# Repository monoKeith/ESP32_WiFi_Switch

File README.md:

# ESP32_WiFi_Switch

This project include hardware design and firmware implementation for a ESP32-S2 powered network accessable on/off switch.

This switch have an 128*64 OLED I2C display to show information. User can turn on/off the switch from HomeKit, physical button, or web interface.

Powered by a [ESP32-S2-Wroom](https://www.espressif.com/sites/default/files/documentation/esp32-s2-wroom_esp32-s2-wroom-i_datasheet_en.pdf). Because the use of ESP32-S2 specific hardware timer library, firmware might have compatibility issue on older (or different) ESP32 models.

## Hardware

PCB printed | PCB etched
:-------------------------:|:-------------------------:
 | 

Soldered | Bread board
:-------------------------:|:-------------------------:
 | 

Single layer PCB designed with [KiCad](https://www.kicad.org/) in `./breakout_board`. This is only useful for starting with only a [module](https://www.espressif.com/en/products/modules), unnecessary if you already have a dev board. Requires ESP32-S2-WROOM library from [this](https://github.com/eggsampler/ESP32-S2-Breakout) breakout board design.

Connected devices includes:

* 3 buttons pull-down to ground (resistors are optional)

* 1 mono-color 128*64 OLED I2C display [like this one](https://www.adafruit.com/product/326) (These are like $2 - $3 each on Aliexpress)

* external circuit to drive a relay (or MOSFET) from a GPIO pin. (I use a transistor to drive a 5V relay)

## Firmware

Firmware was implemented in C++ using PlatformIO arduino framework. Each part of the firmware is run a task of FreeRTOS. PlatformIO was initialized with [adafruit MagTag](https://www.adafruit.com/product/4800) configuration (which uses the same module), because ESP32-S2 Dev Board does not offer support for arduino framework.

Configure properties of firmware in `Firmware/src/config.h` according to how hardwares are connectred, and Wi-Fi credential. (ESP32-S2 allows any 2 GPIO pins to run I2C, connecting I2C display to any 2 GPIO pins should work)

### Functionalities

* [Automatically connect to Wi-Fi](https://randomnerdtutorials.com/esp32-useful-wi-fi-functions-arduino/) with credentials configured in `config.h`

* [Get current time from time server](https://randomnerdtutorials.com/esp32-date-time-ntp-client-server-arduino/)

* Sync time with time server periodically (uses [ESP32-S2 hardware timer](https://github.com/khoih-prog/ESP32TimerInterrupt/blob/master/examples/TimerInterruptTest/TimerInterruptTest.ino))

* [Turn on / off the switch from web interface](https://randomnerdtutorials.com/esp32-web-server-arduino-ide/)

* Turn on / off the switch with buttons, (white = on, gray = off)

* Press black button to cycle through display mode [REGULAR] -> [DEBUG] -> [OFF]

* Show message on screen when switch is being turn on / off, message stay on screen for 3000ms by default (configurable in `config.h`)

### Display

[REGULAR] mode:

* only shows current time

* display message in full screen if any.

[DEBUG] mode:

* on / off status of the switch

* current time

* Wi-Fi connection status, IP address and RSSI

* display message if any, otherwise show the time of last clock synchronization.

* time mark in ms for current message to hit it's 3000ms lifetime

* uptime in ms

REGULAR | REGULAR-MESSAGE| DEBUG
:-------------------------:|:-------------------------:|:-------------------------:
 |  | 

### PlatformIO Libraries

* [esp8266-oled-ssd1306](https://github.com/ThingPulse/esp8266-oled-ssd1306)

* [ESP32TimerInterrupt](https://github.com/khoih-prog/ESP32TimerInterrupt)

* [ESPAsyncWebServer](https://github.com/me-no-dev/ESPAsyncWebServer/)

### HomeBridge Plugin

To make the switch accessable from [iOS Home](https://www.apple.com/ca/ios/home/), a separate [HomeBridge](https://homebridge.io/) server is required. I am running the HomeBridge server on a [RaspberryPi Zero W](https://www.raspberrypi.com/products/raspberry-pi-zero-w/).

Install this plugin: [homebridge-http-switch](https://github.com/Supereg/homebridge-http-switch#readme) in HomeBridge, change settings (fill in the ip address and name):

```
{
    "accessory": "HTTP-SWITCH",
    "name": "<name-display-in-Home>",
    "switchType": "stateful",
    "serialNumber": "<fill-in-anything-here>",
    "onUrl": "http://<ip-of-esp32>:80/homebridge/switch/on",
    "offUrl": "http://<ip-of-esp32>:80/homebridge/switch/off",
    "statusUrl": "http://<ip-of-esp32>:80/homebridge/switch/status"
}
```

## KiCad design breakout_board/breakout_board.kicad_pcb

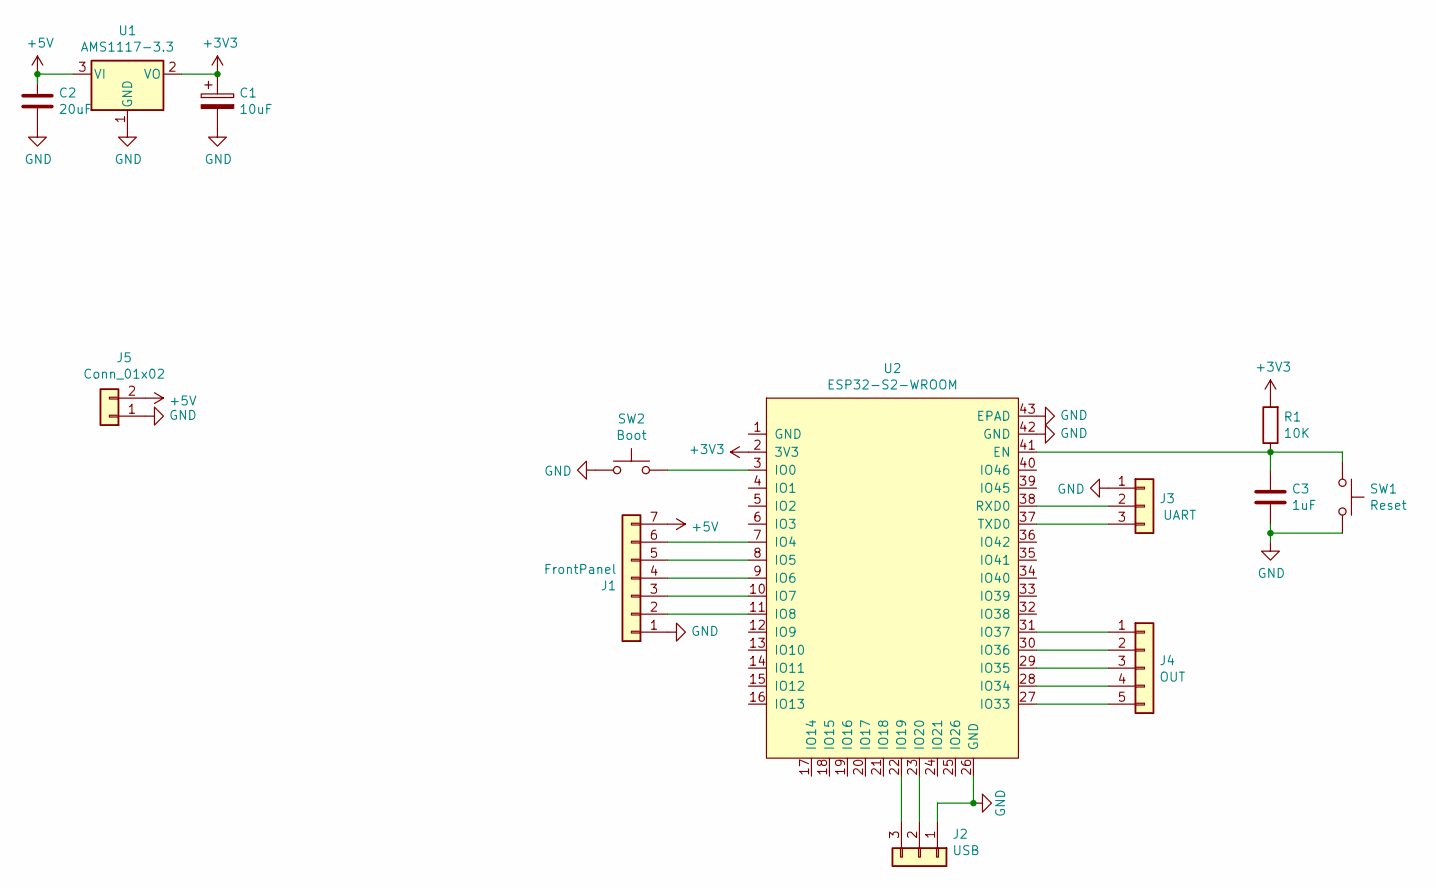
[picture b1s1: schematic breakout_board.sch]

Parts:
C1: 10uF; CP_Elec_5x5.9
C2: 20uF; CP_Elec_5x5.9
C3: 1uF; CP_Elec_5x5.9
J1: FrontPanel; PinHeader_1x07_P2.54mm_Vertical
J2: USB; PinHeader_1x03_P2.54mm_Vertical
J3: UART; PinHeader_1x03_P2.54mm_Vertical
J4: OUT; PinHeader_1x05_P2.54mm_Vertical
J5: Conn_01x02; PinHeader_1x02_P2.54mm_Vertical
R1: 10K; R_Axial_DIN0207_L6.3mm_D2.5mm_P10.16mm_Horizontal
SW1: Reset; SW_Push_1P1T_NO_Vertical_Wuerth_434133025816
SW2: Boot; SW_Push_1P1T_NO_Vertical_Wuerth_434133025816
U1: AMS1117-3.3; SOT-223-3_TabPin2
U2: ESP32-S2-WROOM

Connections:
+3V3: C1.1, R1.2, U1.2 (VO), U2.2 (3V3)
+5V: C2.1, J1.7, J5.2, U1.3 (VI)
GND: C1.2, C2.2, C3.2, J1.1, J2.1, J3.1, J5.1, SW1.2, SW2.1, U1.1 (GND), U2.26 (GND), U2.42 (GND), U2.43 (EPAD)
unnamed: C3.1, R1.1, SW1.1, U2.41 (EN)
unnamed: J1.2, U2.11 (IO8)
unnamed: J1.3, U2.10 (IO7)
unnamed: J1.4, U2.9 (IO6)
unnamed: J1.5, U2.8 (IO5)
unnamed: J1.6, U2.7 (IO4)
unnamed: J2.2, U2.23 (IO20)
unnamed: J2.3, U2.22 (IO19)
unnamed: J3.2, U2.38 (RXD0)
unnamed: J3.3, U2.37 (TXD0)
unnamed: J4.1, U2.31 (IO37)
unnamed: J4.2, U2.30 (IO36)
unnamed: J4.3, U2.29 (IO35)
unnamed: J4.4, U2.28 (IO34)
unnamed: J4.5, U2.27 (IO33)
unnamed: SW2.2, U2.3 (IO0)

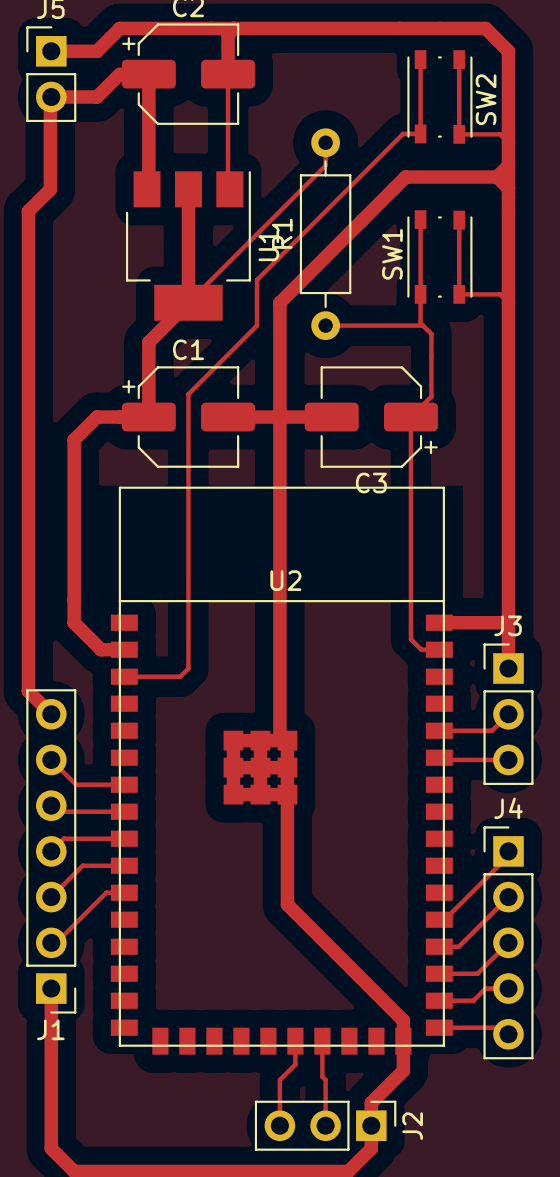
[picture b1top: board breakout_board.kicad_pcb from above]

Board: 2 copper layers, 13 parts (0 on the bottom side), 19 nets.

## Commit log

2021-12-26 Breakout board design, Initialize PIO project
2021-12-26 Change PIO project to Arduino framework
2021-12-26 Create LICENSE
2021-12-26 Auto stash before merge of "main" and "origin/main"
2021-12-26 Separate I2C display to a new Monitor class
2021-12-26 Connect WiFi & Display time
2021-12-27 Migrate display-time to a new State class
2021-12-27 Refactor tab size to 4
2021-12-27 Replace State class with state namespace
2021-12-27 Switch ON/OFF from button press
2021-12-27 Migrate WiFi code to server namespace
2021-12-27 HTTP control with Web UI
2021-12-27 Support direct HTTP control (HomeBridge)
2021-12-27 Fix HomeBridge check status request
2021-12-27 Refactor monitor class -> namespace, new debug screen
2021-12-27 Display mode selector
2021-12-27 Refined UI
2021-12-28 Sync clock periodically
2021-12-28 Display IP and RSSI in Debug screen
2021-12-28 Minor refactors
2021-12-28 Relocate clock to clockControl namespace
2021-12-28 Configurable Y offset
2022-01-04 New breakout board design
2022-01-06 [WIP] can't connect WiFi?
2022-01-06 Minor Tweaks
2022-01-06 [WIP] Connection watchdog
2022-01-06 Fix bug: clock doesn't run
2022-01-06 Minor tweak
2022-01-06 Integrate AsyncWebServer
2022-01-06 Code cleanup
2022-01-06 Include new library in Readme
